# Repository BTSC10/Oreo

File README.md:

# Broos
Beetle-weight Melty Brain Combat Robot.
(dont read me)
(please don't)
Ily's new edit

Name Ideas:
***********
Broos

You spin my head round

Oreo

<name>

Spinn

Oooga Booga

(Atak go) Brrr

Toothless

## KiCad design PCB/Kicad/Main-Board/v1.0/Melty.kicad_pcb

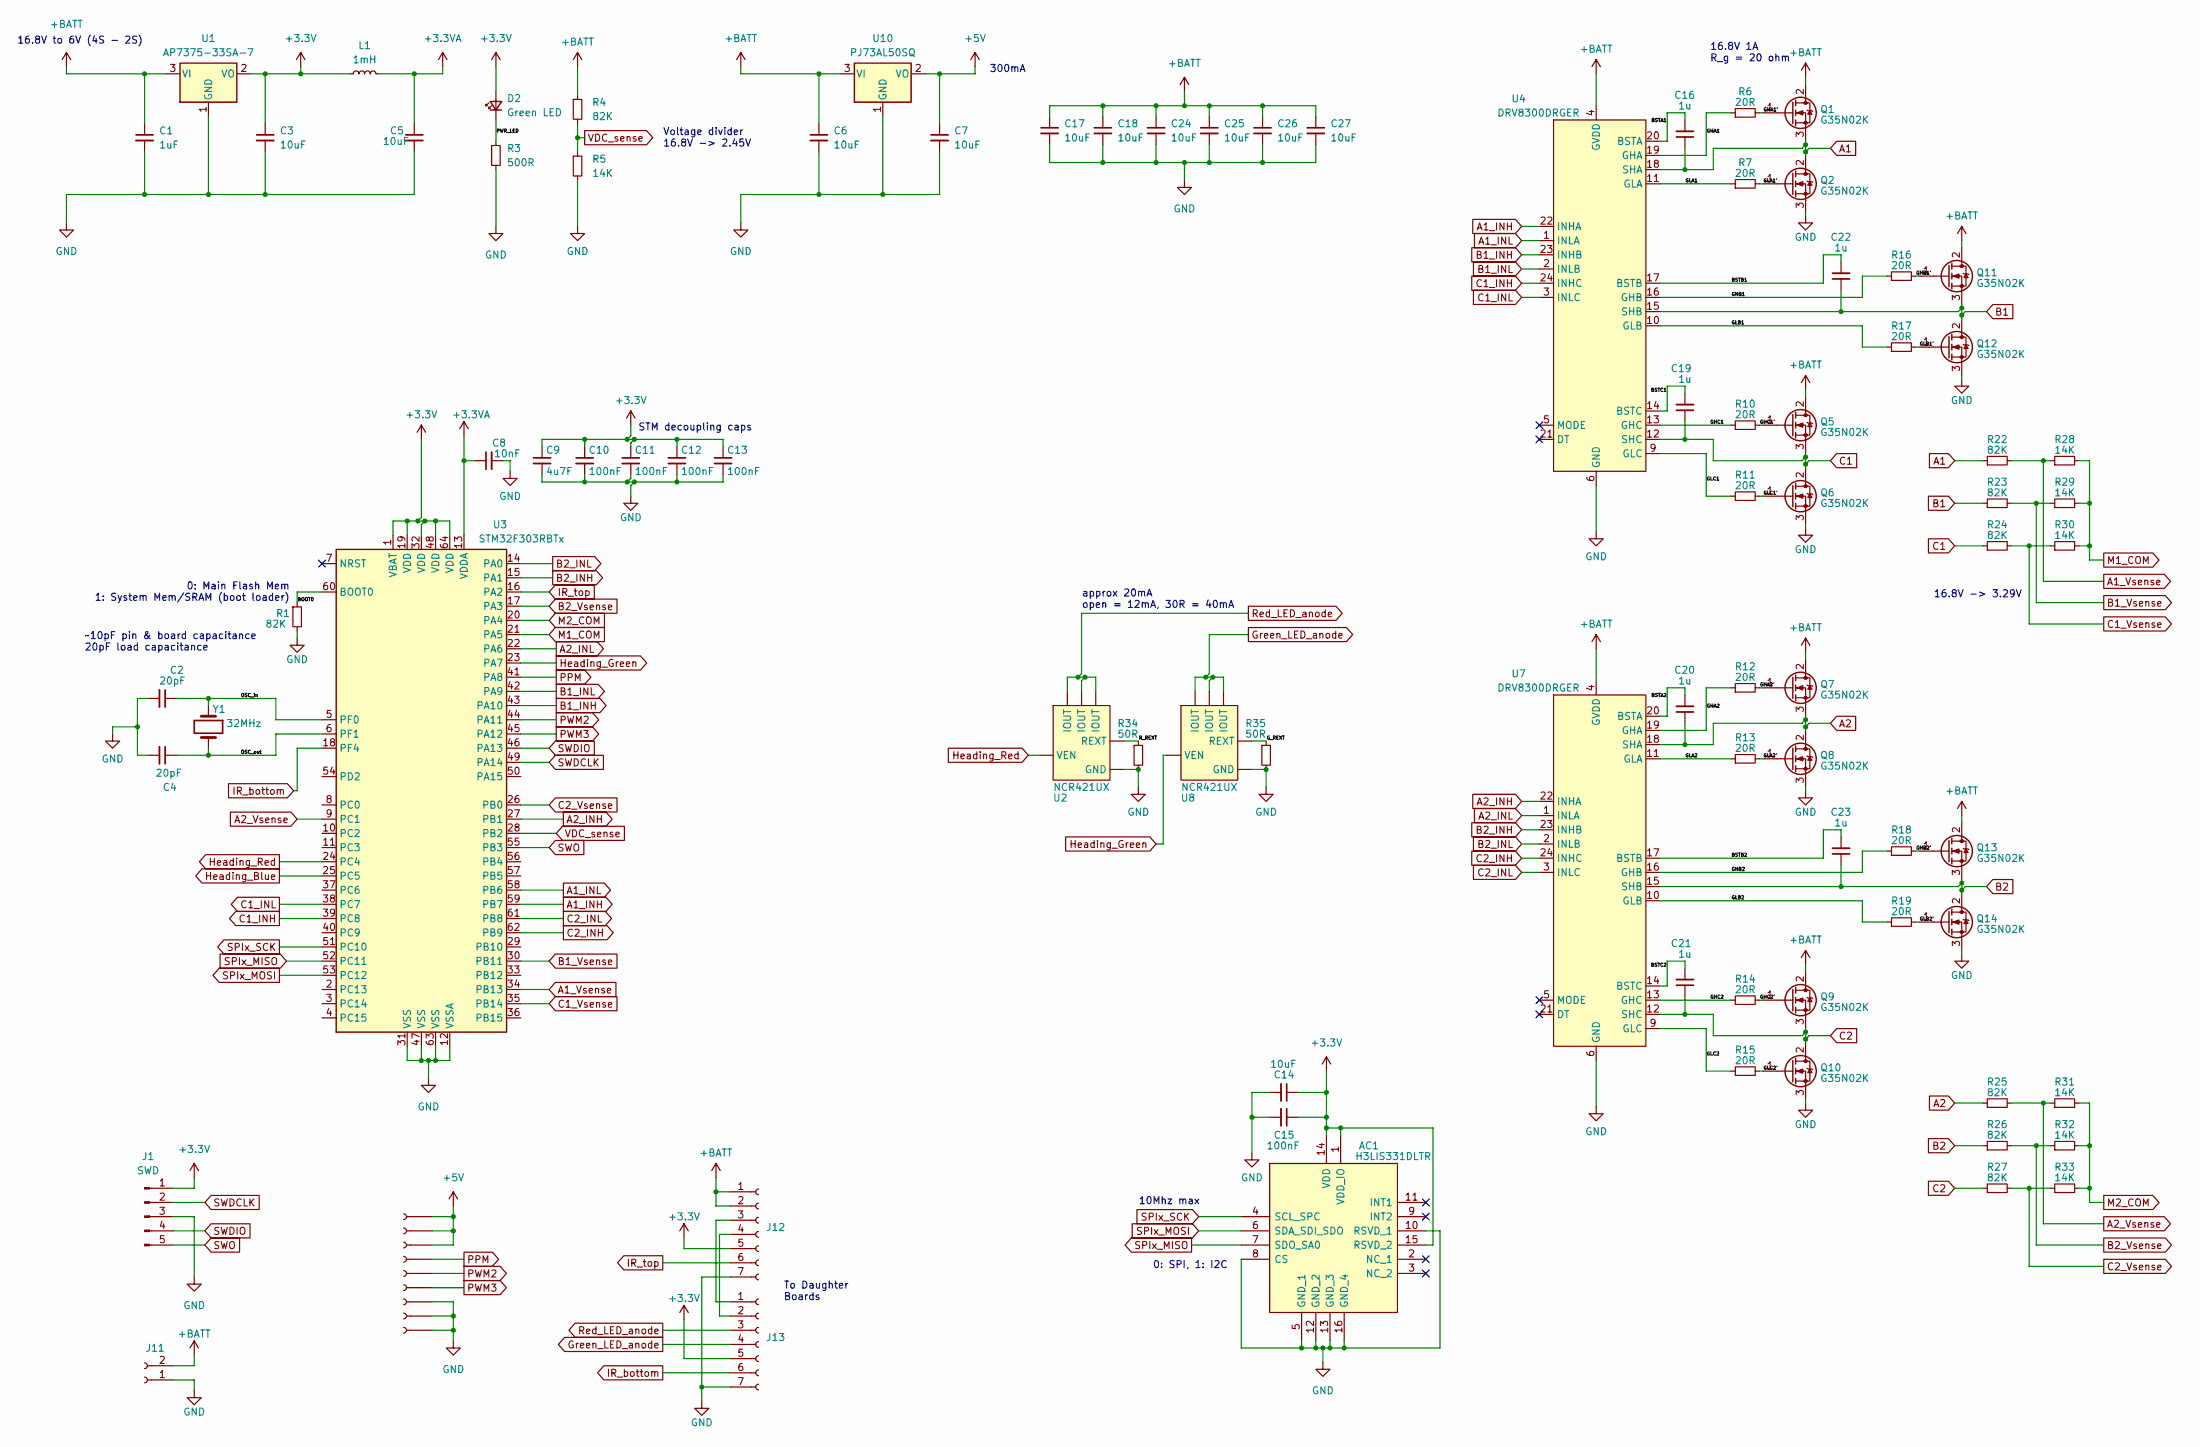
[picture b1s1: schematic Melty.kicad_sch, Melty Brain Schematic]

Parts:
AC1: H3LIS331DLTR; Manufacturer_Part_Number H3LIS331DLTR; Mouser Part Number 511-H3LIS331DLTR
C1: 1uF; C_0805_2012Metric
C2, C4: 20pF; C_0402_1005Metric
C3, C5, C7, C14: 10uF; C_0402_1005Metric
C6, C17, C18, C24, C25, C26, C27: 10uF; C_1206_3216Metric
C8: 10nF; C_0402_1005Metric
C9: 4u7F; C_0603_1608Metric
C10, C11, C12, C13, C15: 100nF; C_0402_1005Metric
C16, C19, C20, C21, C22, C23: 1u; C_0805_2012Metric
D2: Green LED; LED_0603_1608Metric
J1: SWD; PinHeader_1x05_P2.54mm_Vertical
J2, J3, J4, J5, J6, J7, J8, J9, J10: Conn_01x01_Female; SolderWirePad_1x01_SMD_1x2mm
J11: Conn_01x02_Female; PinSocket_1x02_P2.54mm_Vertical
J12, J13: Conn_01x07_Female; PinSocket_1x07_P2.00mm_Vertical
L1: 1mH; L_1210_3225Metric
Q1, Q2, Q5, Q6, Q7, Q8, Q9, Q10, Q11, Q12, Q13, Q14: G35N02K; TO-252-2
R1, R4, R22, R23, R24, R25, R26, R27: 82K; R_0402_1005Metric
R3: 500R; R_0805_2012Metric
R5, R28, R29, R30, R31, R32, R33: 14K; R_0402_1005Metric
R6, R7, R10, R11, R12, R13, R14, R15, R16, R17, R18, R19: 20R; R_0402_1005Metric
R34, R35: 50R
U1: AP7375-33SA-7; SOT-23
U2, U8: NCR421UX; TSOP-6_1.65x3.05mm_P0.95mm
U3: STM32F303RBTx; LQFP-64_10x10mm_P0.5mm
U4, U7: DRV8300DRGER; VQFN-24-1EP_4x4mm_P0.5mm_EP2.45x2.45mm
U10: PJ73AL50SQ; SOT-89-3
Y1: 32MHz; Crystal_SMD_3225-4Pin_3.2x2.5mm

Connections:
+3.3VA: C5.1, C8.1, L1.2, U3.13 (VDDA)
+3V3: AC1.1 (VDD_IO), AC1.14 (VDD), AC1.15 (RSVD_2), C3.1, C9.1, C10.1, C11.1, C12.1, C13.1, C14.1, C15.1, D2.2 (A), J1.1, J12.5, J13.5, L1.1, U1.2 (VO), U3.1 (VBAT), U3.19 (VDD), U3.32 (VDD), U3.48 (VDD), U3.64 (VDD)
+5V: C7.1, J2.1, J3.1, J4.1, U10.2 (VO)
+BATT: C1.1, C6.1, C17.1, C18.1, C24.1, C25.1, C26.1, C27.1, J11.2, J12.1, J12.2, Q1.2 (D), Q5.2 (D), Q7.2 (D), Q9.2 (D), Q11.2 (D), Q13.2 (D), R4.1, U1.3 (VI), U4.4 (GVDD), U7.4 (GVDD), U10.3 (VI)
/BOOT0: R1.1, U3.60 (BOOT0)
/BSTA1: C16.2, U4.20 (BSTA)
/BSTA2: C20.2, U7.20 (BSTA)
/BSTB1: C22.2, U4.17 (BSTB)
/BSTB2: C23.2, U7.17 (BSTB)
/BSTC1: C19.2, U4.14 (BSTC)
/BSTC2: C21.2, U7.14 (BSTC)
/GHA1: R6.1, U4.19 (GHA)
/GHA1': Q1.1 (G), R6.2
/GHA2: R12.1, U7.19 (GHA)
/GHA2': Q7.1 (G), R12.2
/GHB1: R16.1, U4.16 (GHB)
/GHB1': Q11.1 (G), R16.2
/GHB2: R18.1, U7.16 (GHB)
/GHB2': Q13.1 (G), R18.2
/GHC1: R10.1, U4.13 (GHC)
/GHC1': Q5.1 (G), R10.2
/GHC2: R14.1, U7.13 (GHC)
/GHC2': Q9.1 (G), R14.2
/GLA1: R7.1, U4.11 (GLA)
/GLA1': Q2.1 (G), R7.2
/GLA2: R13.1, U7.11 (GLA)
/GLA2': Q8.1 (G), R13.2
/GLB1: R17.1, U4.10 (GLB)
/GLB1': Q12.1 (G), R17.2
/GLB2: R19.1, U7.10 (GLB)
/GLB2': Q14.1 (G), R19.2
/GLC1: R11.1, U4.9 (GLC)
/GLC1': Q6.1 (G), R11.2
/GLC2: R15.1, U7.9 (GLC)
/GLC2': Q10.1 (G), R15.2
/G_REXT: R35.1, U8.6 (REXT)
/OSC_in: C2.1, U3.5 (PF0), Y1.1
/OSC_out: C4.1, U3.6 (PF1), Y1.3
/PWR_LED: D2.1 (K), R3.1
/R_REXT: R34.1, U2.6 (REXT); also elsewhere on the board
A1: C16.1, Q1.3 (S), Q2.2 (D), R22.1, U4.18 (SHA)
A1_INH: U3.59 (PB7), U4.22 (INHA)
A1_INL: U3.58 (PB6), U4.1 (INLA)
A1_Vsense: R22.2, R28.1, U3.34 (PB13)
A2: C20.1, Q7.3 (S), Q8.2 (D), R25.1, U7.18 (SHA)
A2_INH: U3.27 (PB1), U7.22 (INHA)
A2_INL: U3.22 (PA6), U7.1 (INLA)
A2_Vsense: R25.2, R31.1, U3.9 (PC1)
B1: C22.1, Q11.3 (S), Q12.2 (D), R23.1, U4.15 (SHB)
B1_INH: U3.43 (PA10), U4.23 (INHB)
B1_INL: U3.42 (PA9), U4.2 (INLB)
B1_Vsense: R23.2, R29.1, U3.30 (PB11)
B2: C23.1, Q13.3 (S), Q14.2 (D), R26.1, U7.15 (SHB)
B2_INH: U3.15 (PA1), U7.23 (INHB)
B2_INL: U3.14 (PA0), U7.2 (INLB)
B2_Vsense: R26.2, R32.1, U3.17 (PA3)
C1: C19.1, Q5.3 (S), Q6.2 (D), R24.1, U4.12 (SHC)
C1_INH: U3.39 (PC8), U4.24 (INHC)
C1_INL: U3.38 (PC7), U4.3 (INLC)
C1_Vsense: R24.2, R30.1, U3.35 (PB14)
C2: C21.1, Q9.3 (S), Q10.2 (D), R27.1, U7.12 (SHC)
C2_INH: U3.62 (PB9), U7.24 (INHC)
C2_INL: U3.61 (PB8), U7.3 (INLC)
C2_Vsense: R27.2, R33.1, U3.26 (PB0)
GND: AC1.5 (GND_1), AC1.8 (CS), AC1.10 (RSVD_1), AC1.12 (GND_2), AC1.13 (GND_3), AC1.16 (GND_4), C1.2, C2.2, C3.2, C4.2, C5.2, C6.2, C7.2, C8.2, C9.2, C10.2, C11.2, C12.2, C13.2, C14.2, C15.2, C17.2, C18.2, C24.2, C25.2, C26.2, C27.2, J1.3, J8.1, J9.1, J10.1, J11.1, J12.7, J13.7, Q2.3 (S), Q6.3 (S), Q8.3 (S), Q10.3 (S), Q12.3 (S), Q14.3 (S), R1.2, R3.2, R5.2, R34.2, R35.2, U1.1 (GND), U2.4 (GND), U3.12 (VSSA), U3.31 (VSS), U3.47 (VSS), U3.63 (VSS), U4.6 (GND), U7.6 (GND), U8.4 (GND), U10.1 (GND); also elsewhere on the board
Green_LED_anode: J13.4, U8.2 (IOUT), U8.3 (IOUT), U8.5 (IOUT)
Heading_Blue: U3.25 (PC5)
Heading_Green: U3.23 (PA7), U8.1 (VEN)
Heading_Red: U2.1 (VEN), U3.24 (PC4)
IR_bottom: J13.6, U3.18 (PF4)
IR_top: J12.6, U3.16 (PA2)
M1_COM: R28.2, R29.2, R30.2, U3.21 (PA5)
M2_COM: R31.2, R32.2, R33.2, U3.20 (PA4)
unnamed: J12.3, J13.1
unnamed: J12.4, J13.2
PPM: J5.1, U3.41 (PA8)
PWM2: J6.1, U3.44 (PA11)
PWM3: J7.1, U3.45 (PA12)
Red_LED_anode: J13.3, U2.2 (IOUT), U2.3 (IOUT), U2.5 (IOUT)
SPIx_MISO: AC1.7 (SDO_SA0), U3.52 (PC11)
SPIx_MOSI: AC1.6 (SDA_SDI_SDO), U3.53 (PC12)
SPIx_SCK: AC1.4 (SCL_SPC), U3.51 (PC10)
SWDCLK: J1.2, U3.49 (PA14)
SWDIO: J1.4, U3.46 (PA13)
SWO: J1.5, U3.55 (PB3)
VDC_sense: R4.2, R5.1, U3.28 (PB2)

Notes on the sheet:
16.8V 1A R_g = 20 ohm
To Daughter Boards
16.8V -> 3.29V
~10pF pin & board capacitance 20pF load capacitance
300mA
approx 20mA open = 12mA, 30R = 40mA
10Mhz max
STM decoupling caps
Voltage divider 16.8V -> 2.45V
16.8V to 6V (4S - 2S)
0: SPI, 1: I2C
0: Main Flash Mem 1: System Mem/SRAM (boot loader)

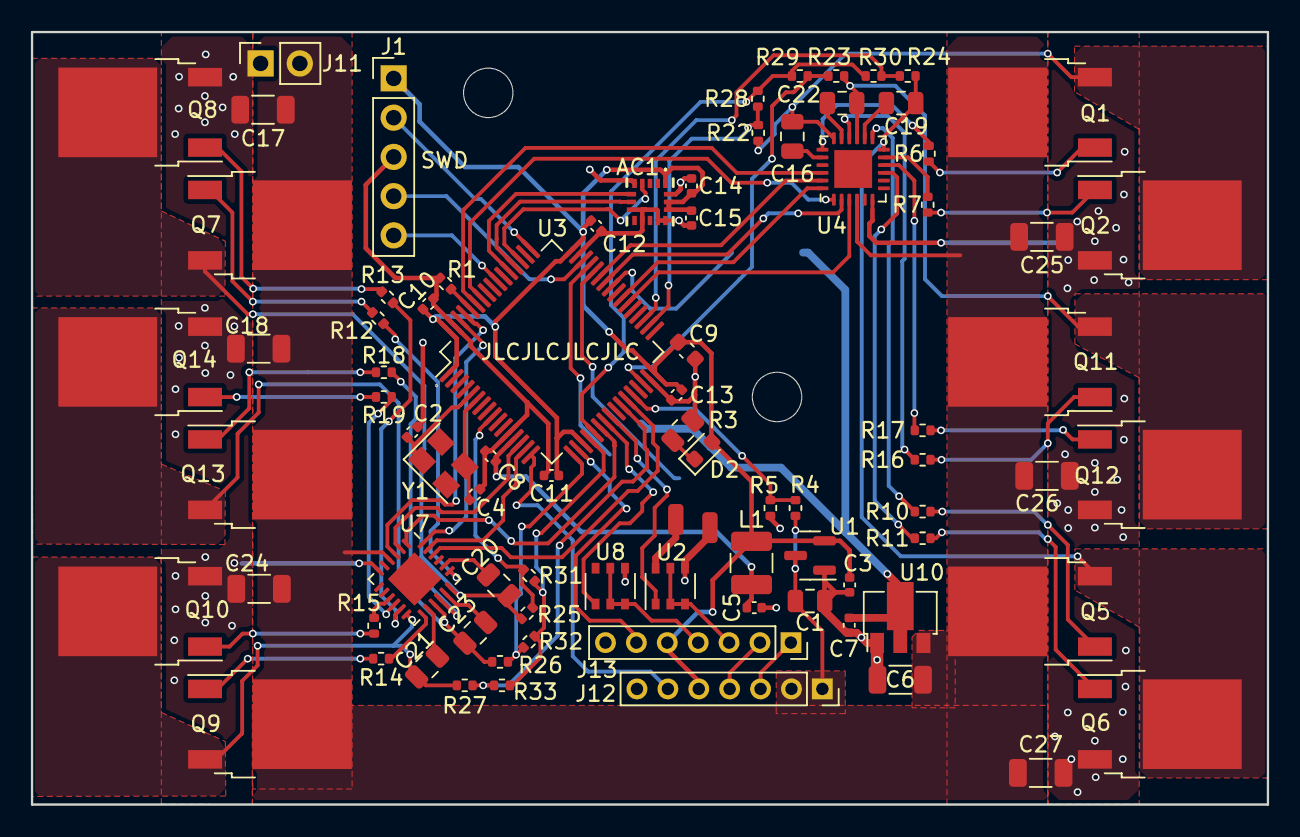
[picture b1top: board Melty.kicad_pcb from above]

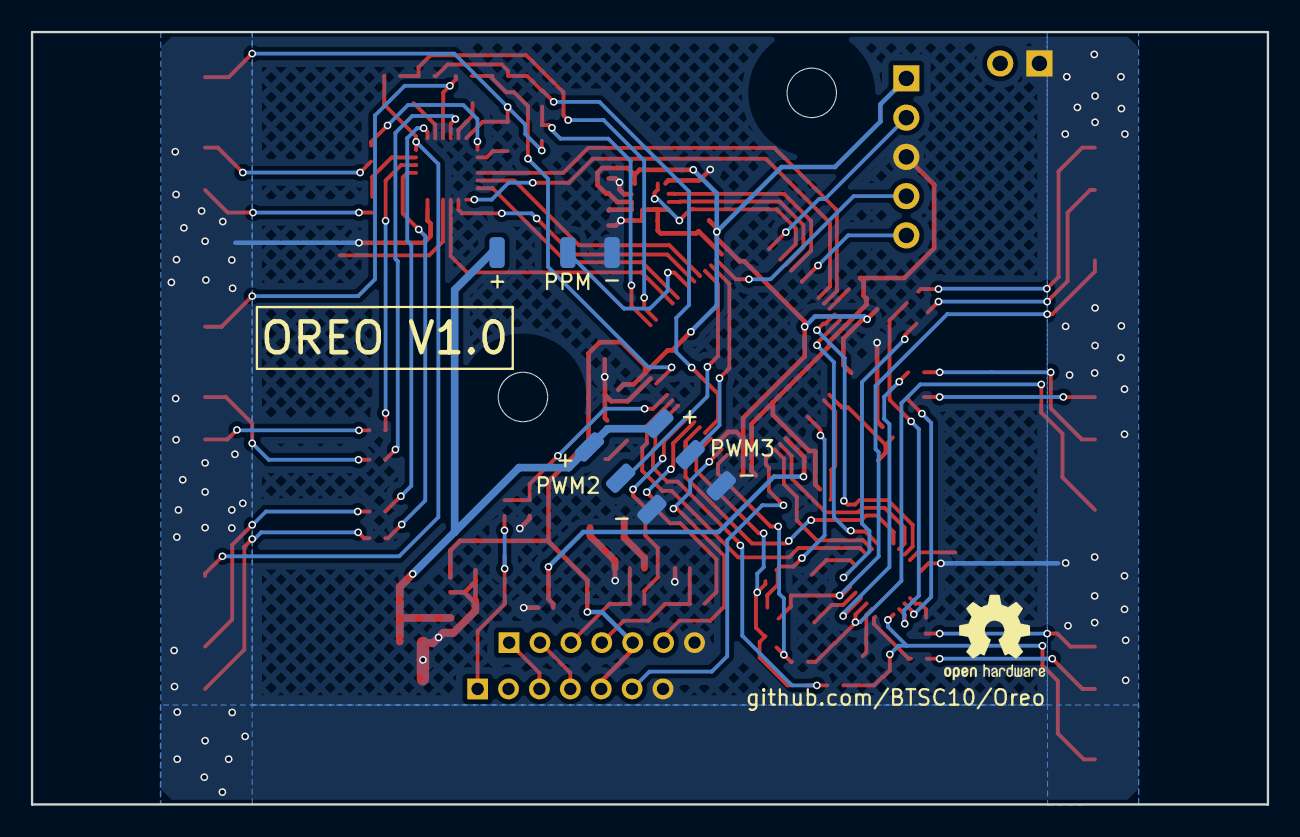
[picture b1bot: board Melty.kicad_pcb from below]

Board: 2 copper layers, 80.0 x 50.0 mm, 93 parts (9 on the bottom side), 84 nets.

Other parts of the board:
J14, J15: Conn_01x01_Female; SolderWirePad_1x01_SMD_1x2mm

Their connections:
/R_REXT: J14.1; also elsewhere on the board
GND: J15.1; also elsewhere on the board

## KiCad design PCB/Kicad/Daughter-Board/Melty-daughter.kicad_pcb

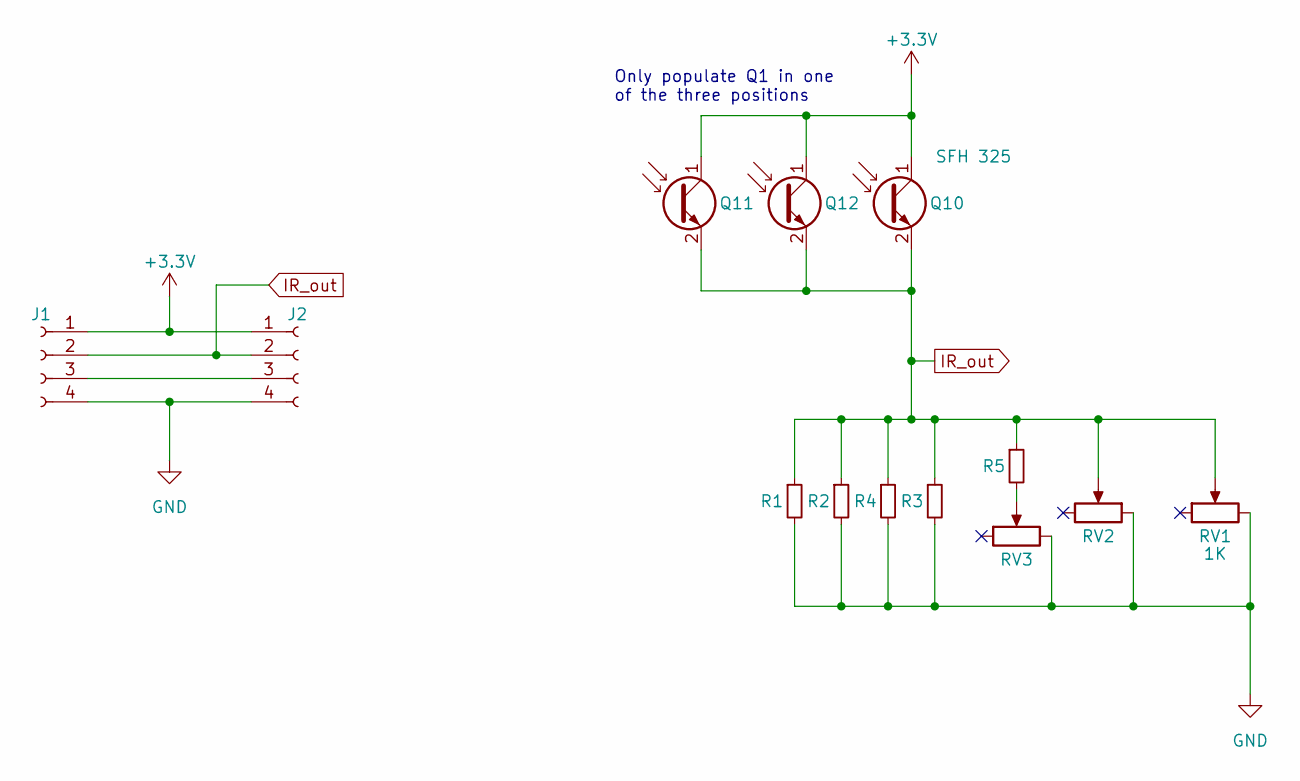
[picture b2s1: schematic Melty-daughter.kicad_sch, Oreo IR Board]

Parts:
J1, J2: Conn_01x04_Female; PinHeader_1x04_P2.54mm_Vertical
Q10, Q11, Q12: SFH 325; SFH325FA34Z
R1: R; R_0603_1608Metric_Pad0.98x0.95mm_HandSolder
R2, R4: R_Small; R_0805_2012Metric_Pad1.20x1.40mm_HandSolder
R3, R5: R_Small; R_Axial_DIN0204_L3.6mm_D1.6mm_P7.62mm_Horizontal
RV1, RV3: 1K; Potentiometer_Bourns_TC42_Horizontal
RV2: 1K; PinHeader_1x03_P2.54mm_Vertical

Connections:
+3V3: J1.1, J2.1, Q10.1 (C), Q11.1 (C), Q12.1 (C)
GND: J1.4, J2.4, R1.2, R2.2, R3.2, R4.2, RV1.3, RV2.1, RV3.3; also elsewhere on the board
IR_out: J1.2, J2.2, Q10.2 (E), Q11.2 (E), Q12.2 (E), R1.1, R2.1, R3.1, R4.1, R5.1, RV1.2, RV2.2; also elsewhere on the board
unnamed: J1.3, J2.3
unnamed: R5.2, RV3.2

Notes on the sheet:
Only populate Q1 in one of the three positions

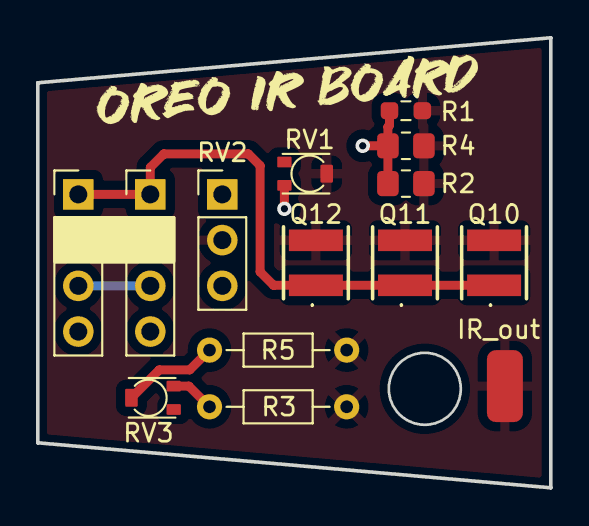
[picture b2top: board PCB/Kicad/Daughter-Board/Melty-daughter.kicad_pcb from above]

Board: 2 copper layers, 28.5 x 25.0 mm, 15 parts (0 on the bottom side), 5 nets.

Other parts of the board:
P1, P2: SolderWirePad_1x01_SMD_1x2mm

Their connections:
GND: P2.1; also elsewhere on the board
IR_out: P1.1; also elsewhere on the board

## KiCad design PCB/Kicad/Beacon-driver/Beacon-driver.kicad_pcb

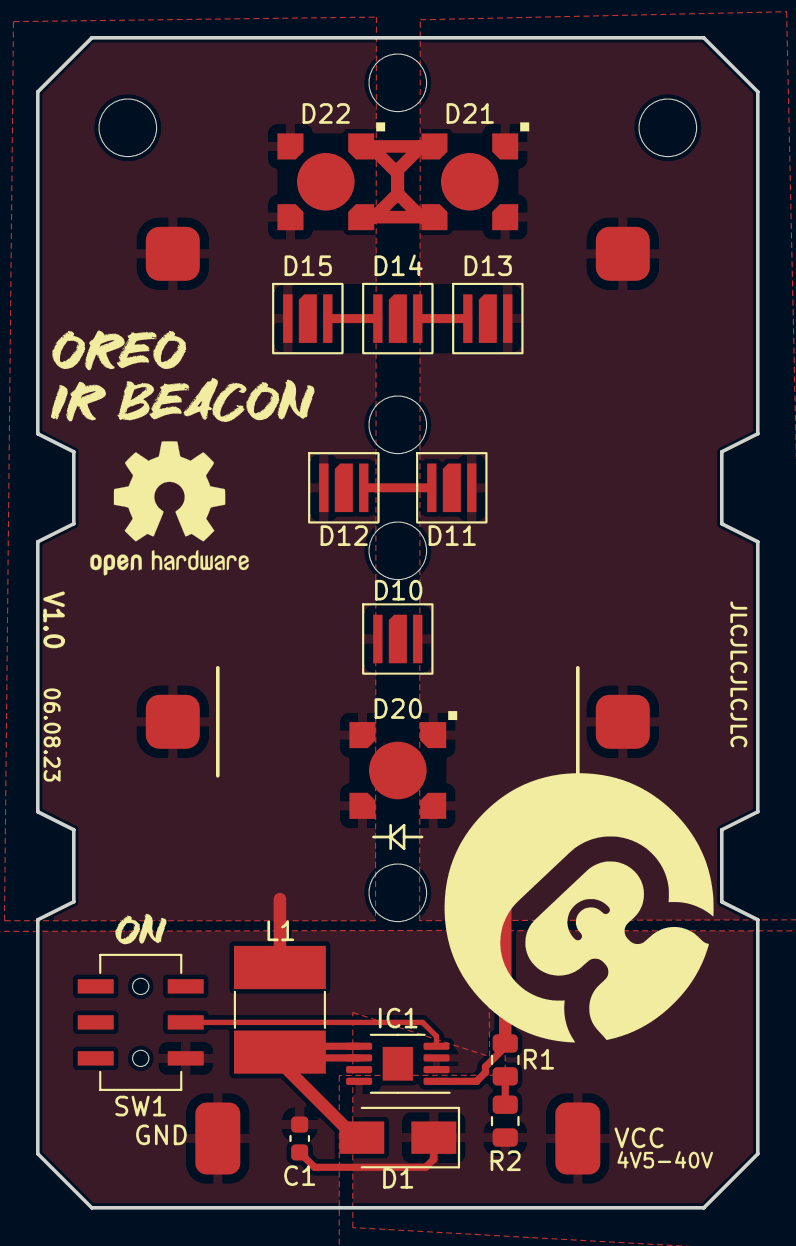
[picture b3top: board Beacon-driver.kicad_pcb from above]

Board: 2 copper layers, 40.0 x 65.0 mm, 22 parts (0 on the bottom side), 11 nets.

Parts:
C1: 10uF; C_0603_1608Metric
D1: ES2AA; D_SMA
D10, D11, D12, D13, D14, D15: LED; SE03-EMC3838A-C90-940 (jank led)
D20, D21, D22: LZ1-00R702
GND: SolderWirePad_1x01_SMD_1x2mm
IC1: AL8860MP-13; MSOP-8-1EP_3x3mm_P0.65mm_EP1.68x1.88mm
L1: 47uH; VLS-EX-H
R1, R2: 0R1; R_0805_2012Metric
SW1: TA-3539S-A1; TA-3539S-A1 switch
VCC: SolderWirePad_1x01_SMD_1x2mm
VCC#2, VCC#3, VCC#4, VCC#5: SolderWirePad_1x01_SMD_1x2mm

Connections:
/Feedback_V: D10.2 (A), D11.2 (A), D13.2 (A), D20.2 (A), D21.2 (A), IC1.1 (SET), R1.2, VCC#2.1, VCC#3.1
/LED_Cathode: D10.1 (K), D12.1 (K), D15.1 (K), D20.1 (K), D22.1 (K), L1.1, VCC.1, VCC#4.1
/SW: D1.2 (A), IC1.5 (SW_1), IC1.6 (SW_2), L1.2
GND: C1.2, GND.1, IC1.2 (GND_1), IC1.3 (GND_2), SW1.4 (A)
unnamed: D11.1 (K), D12.2 (A)
unnamed: D13.1 (K), D14.2 (A)
unnamed: D14.1 (K), D15.2 (A)
unnamed: D21.1 (K), D22.2 (A)
unnamed: IC1.4 (CTRL), SW1.5 (B)
unnamed: R1.1, R2.2
VCC: C1.1, D1.1 (K), IC1.8 (VIN), R2.1, VCC#5.1

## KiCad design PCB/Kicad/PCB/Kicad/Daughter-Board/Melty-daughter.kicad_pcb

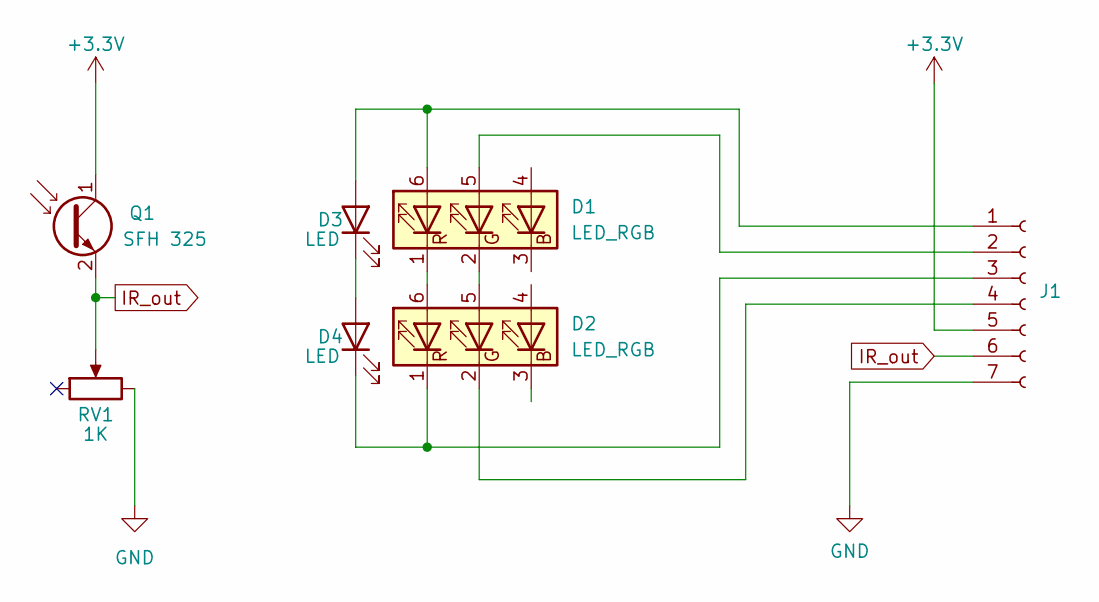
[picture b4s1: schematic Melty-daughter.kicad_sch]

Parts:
D1, D2: LED_RGB; LED_RGB_Harvatek_B3803FCH
D3, D4: LED; LED_D3.0mm
J1: Conn_01x07_Female; PinSocket_1x07_P2.00mm_Vertical
Q1: SFH 325; SFH325FA34Z
RV1: 1K; Potentiometer_Bourns_TC42_Horizontal

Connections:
+3V3: J1.5, Q1.1 (C)
GND: J1.7, RV1.3
IR_out: J1.6, Q1.2 (E), RV1.2
unnamed: D1.1 (RK), D2.6 (RA)
unnamed: D1.2 (GK), D2.5 (GA)
unnamed: D1.5 (GA), J1.2
unnamed: D1.6 (RA), D3.2 (A), J1.1
unnamed: D2.1 (RK), D4.1 (K), J1.3
unnamed: D2.2 (GK), J1.4
unnamed: D3.1 (K), D4.2 (A)

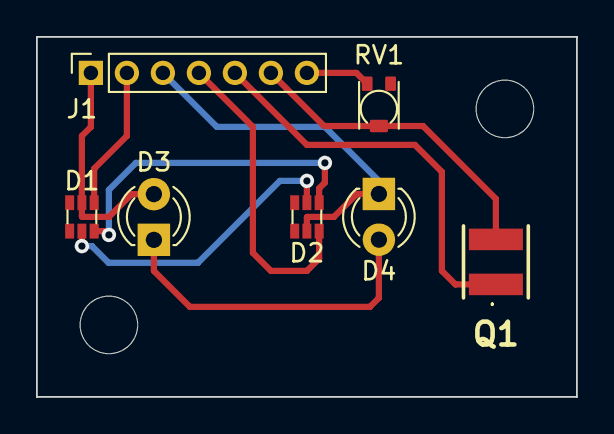
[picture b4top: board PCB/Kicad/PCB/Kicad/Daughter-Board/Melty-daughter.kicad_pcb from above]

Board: 2 copper layers, 30.0 x 20.0 mm, 7 parts (0 on the bottom side), 10 nets.

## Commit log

2022-11-13 initial schematic commit
    First draft for the custom PCB schematics
2022-12-06 Added BOM
2022-12-09 updated BOM
2022-12-09 Updated PCB files
    updated PCB files with a semi final version of the schematic and PCB design for Oreo
2022-12-09 Updated CAD
    Added Solidworks files with rough mechanical construction of the bot
2023-02-22 Updated CAD (v2)
2023-02-22 Updated BOM
    added weight calculations
2023-03-05 Final V1.0 Oreo main PCB
2023-03-05 Updated BOM
    marked components that have arrived
2023-03-05 CAD V2.0
2023-03-07 Added front fab Layer
2023-03-07 Added front fab sheet
2023-03-08 Add melty render
2023-03-08 Update README.md
    Added name ideas
2023-03-12 Added Toothless
2023-06-01 Add Beacon Driver components
2023-06-12 Add Beacon driver files
    Add schematic for the circuit that will drive the high power IR beacon LED.
    Add initial tests of the prototype circuit.
2023-08-08 Add Beacon schematic and PCB design
    Add Kicad files for the schematic and PCB of the beacon circuit
2023-08-08 Add IR Board schematic and PCB design
    Add kicad files for the schematic and PCB of the IR Board.
2023-08-08 Add Main Board schematic and PCB design
    Add kicad files for the Main Board schematic and PCB.
2023-08-08 Separate BOM for each PCB
    Add separate BOM for the Main Board, IR Board, and IR Beacon
2023-08-15 Add /Misc and Antihero font
